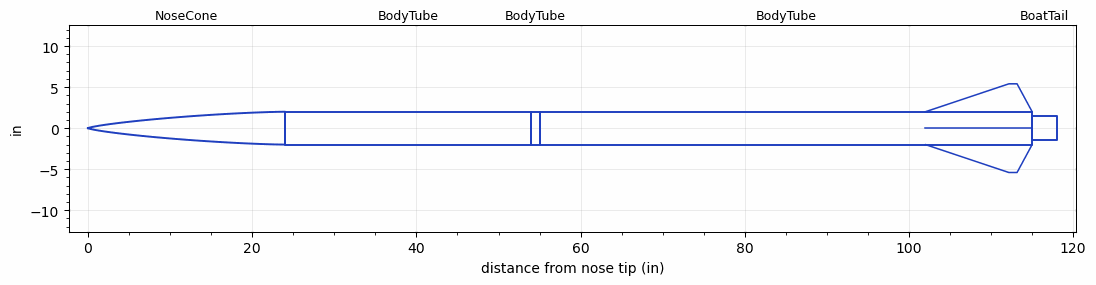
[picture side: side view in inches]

<RASAeroDocument>
 <FileVersion>2</FileVersion>
 <RocketDesign>
  <NoseCone>
   <Length>24</Length>
   <Diameter>4</Diameter>
   <Shape>Von Karman Ogive</Shape>
   <Location>0</Location>
  </NoseCone>
  <BodyTube>
   <Length>29.9999</Length>
   <Diameter>4</Diameter>
   <Location>24</Location>
  </BodyTube>
  <BodyTube>
   <Length>1</Length>
   <Diameter>4</Diameter>
   <Location>53.9999</Location>
  </BodyTube>
  <BodyTube>
   <Length>59.9999</Length>
   <Diameter>4</Diameter>
   <RailGuideDiameter>0.62</RailGuideDiameter>
   <RailGuideHeight>0.4495</RailGuideHeight>
   <Location>54.9999</Location>
   <Fin>
    <Count>4</Count>
    <Chord>13</Chord>
    <Span>3.4</Span>
    <SweepDistance>10.1615</SweepDistance>
    <TipChord>1</TipChord>
    <Thickness>0.28</Thickness>
    <Location>13</Location>
    <AirfoilSection>Subsonic NACA</AirfoilSection>
   </Fin>
  </BodyTube>
  <BoatTail>
   <Length>3</Length>
   <Diameter>3</Diameter>
   <RearDiameter>3</RearDiameter>
   <Location>114.9998</Location>
  </BoatTail>
  <Surface>Camouflage Paint</Surface>
  <CD>0</CD>
  <ModifiedBarrowman>False</ModifiedBarrowman>
  <Turbulence>False</Turbulence>
  <UseBooster1>False</UseBooster1>
  <UseBooster2>False</UseBooster2>
 </RocketDesign>
 <LaunchSite>
  <Altitude>4595.0001</Altitude>
  <Pressure>25.2818</Pressure>
  <RodAngle>0</RodAngle>
  <RodLength>203.9996</RodLength>
  <Temperature>42.6135</Temperature>
  <WindSpeed>0.2237</WindSpeed>
 </LaunchSite>
 <Recovery>
  <Altitude1>1000</Altitude1>
  <Altitude2>656.168</Altitude2>
  <DeviceType1>Parachute</DeviceType1>
  <DeviceType2>Parachute</DeviceType2>
  <Event1>True</Event1>
  <Event2>True</Event2>
  <Size1>95.9998</Size1>
  <Size2>29.9999</Size2>
  <EventType1>Altitude</EventType1>
  <EventType2>Apogee</EventType2>
  <CD1>0.8</CD1>
  <CD2>0</CD2>
 </Recovery>
 <SimulationList>
  <Simulation>
   <SustainerLaunchWt>51.237</SustainerLaunchWt>
   <SustainerCG>75.6933</SustainerCG>
   <SustainerIgnitionDelay>0</SustainerIgnitionDelay>
   <Booster1SeparationDelay>0</Booster1SeparationDelay>
   <Booster1IgnitionDelay>0</Booster1IgnitionDelay>
   <IncludeBooster1>False</IncludeBooster1>
   <Booster2Delay>0</Booster2Delay>
   <IncludeBooster2>False</IncludeBooster2>
  </Simulation>
  <Simulation>
   <SustainerLaunchWt>51.237</SustainerLaunchWt>
   <SustainerCG>75.6933</SustainerCG>
   <SustainerIgnitionDelay>0</SustainerIgnitionDelay>
   <Booster1SeparationDelay>0</Booster1SeparationDelay>
   <Booster1IgnitionDelay>0</Booster1IgnitionDelay>
   <IncludeBooster1>False</IncludeBooster1>
   <Booster2Delay>0</Booster2Delay>
   <IncludeBooster2>False</IncludeBooster2>
  </Simulation>
  <Simulation>
   <SustainerLaunchWt>51.237</SustainerLaunchWt>
   <SustainerCG>75.6933</SustainerCG>
   <SustainerIgnitionDelay>0</SustainerIgnitionDelay>
   <Booster1SeparationDelay>0</Booster1SeparationDelay>
   <Booster1IgnitionDelay>0</Booster1IgnitionDelay>
   <IncludeBooster1>False</IncludeBooster1>
   <Booster2Delay>0</Booster2Delay>
   <IncludeBooster2>False</IncludeBooster2>
  </Simulation>
  <Simulation>
   <SustainerLaunchWt>51.237</SustainerLaunchWt>
   <SustainerCG>75.6933</SustainerCG>
   <SustainerIgnitionDelay>0</SustainerIgnitionDelay>
   <Booster1SeparationDelay>0</Booster1SeparationDelay>
   <Booster1IgnitionDelay>0</Booster1IgnitionDelay>
   <IncludeBooster1>False</IncludeBooster1>
   <Booster2Delay>0</Booster2Delay>
   <IncludeBooster2>False</IncludeBooster2>
  </Simulation>
  <Simulation>
   <SustainerLaunchWt>51.237</SustainerLaunchWt>
   <SustainerCG>75.6933</SustainerCG>
   <SustainerIgnitionDelay>0</SustainerIgnitionDelay>
   <Booster1SeparationDelay>0</Booster1SeparationDelay>
   <Booster1IgnitionDelay>0</Booster1IgnitionDelay>
   <IncludeBooster1>False</IncludeBooster1>
   <Booster2Delay>0</Booster2Delay>
   <IncludeBooster2>False</IncludeBooster2>
  </Simulation>
 </SimulationList>
</RASAeroDocument>
